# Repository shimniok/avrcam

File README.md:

# avrcam

Fork of JROBOT AVRcam by Michael Shimniok

AVRcam Hardware and Embedded Software Copyright © 2004 John Orlando
AVRcamVIEW PC Software Copyright © 2004 Brent Taylor

The AVRcam system is distributed in the hope that it will be useful. However, no warranties,
either expressed or implied, are made regarding the operation, use or results of this system. The
AVRcam should not be used in any life-critical applications.

The AVRcam is an embedded machine vision system based on an Omnivision OV6620 CMOS image sensor and ATmega microcontroller that can perform simple color
blob tracking. It is designed to be a subsystem to a more complex embedded project and uses a standard TTL serial interface. The AVRcam also comes with
standalone, cross-platform client software to interface with a computer.

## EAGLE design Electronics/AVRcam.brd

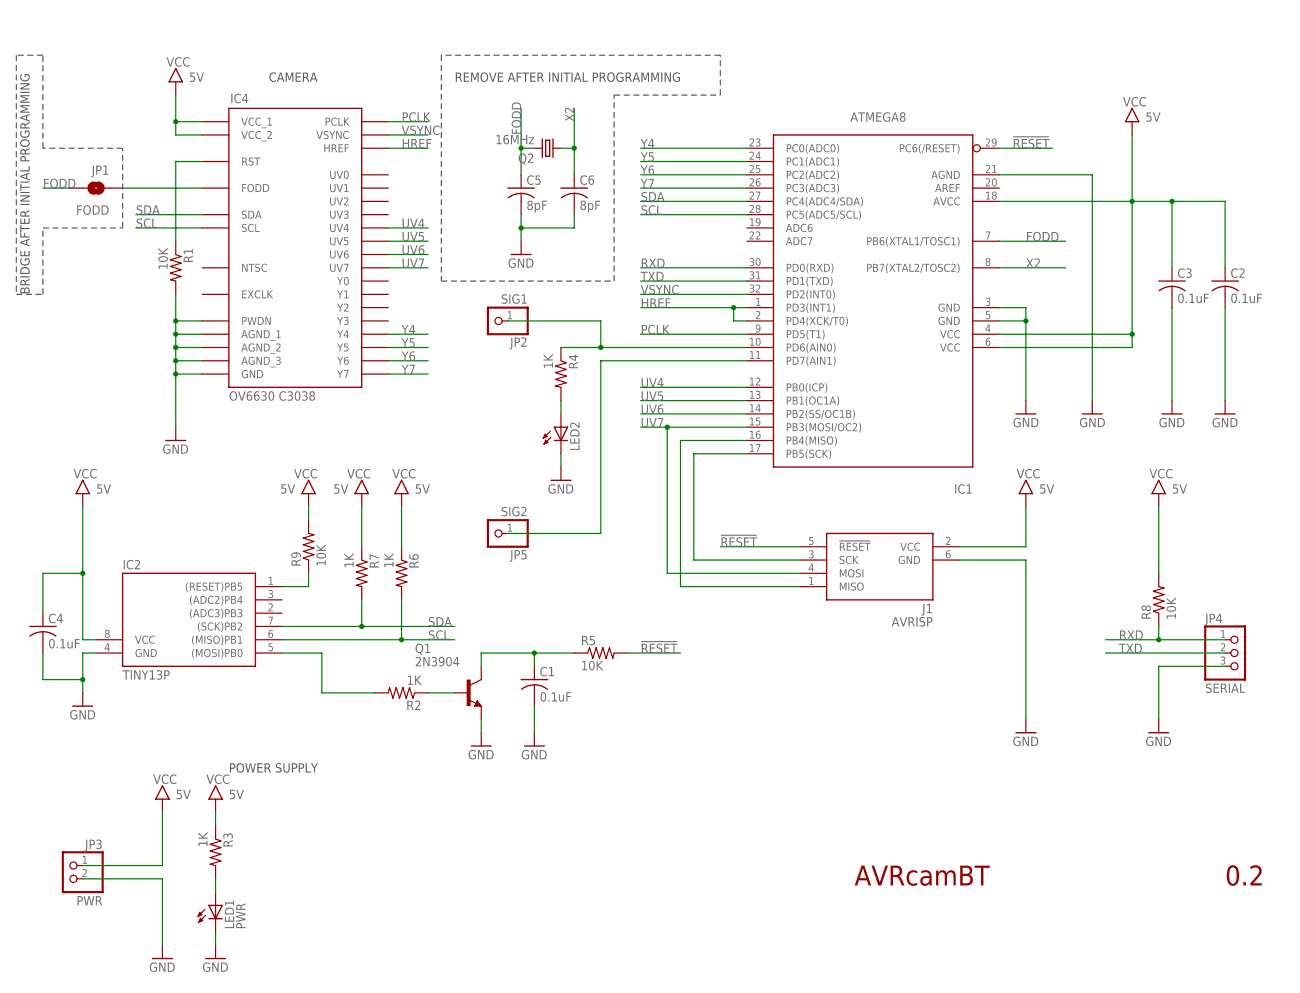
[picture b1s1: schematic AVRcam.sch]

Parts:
C1, C2, C3, C4: 0.1uF; C0603; PARTNO CC0603ZRY5V9BB104
C5, C6: 8pF; C0603; PARTNO C1608C0G1H080D
IC1: ATMEGA8; TQFP32-08; PARTNO ATMEGA8A-AU
IC2: TINY13P; DIL08; PARTNO ATTINY13V-10PU
IC4: OV6630 C3038; C3038/C3X88/C3088
J1: AVRISP; CON6P2R
JP1: FODD; SJ_2S-NO
JP2: SIG1; 1X01
JP3: PWR; 1X02-S
JP4: SERIAL; 1X03-S
JP5: SIG2; 1X01
LED1: PWR; CHIP-LED0805; PARTNO APT2012EC
LED2: LEDCHIP-LED0805; CHIP-LED0805; PARTNO APT2012SGC
Q1: 2N3904; SOT-23; PARTNO MMBT3904-7-F
Q2: 16MHz; NDK_2PAD_5X3; PARTNO NX5032GA-16.000000MHZ-LN-CD-1
R1, R5, R8, R9: 10K; R0603; PARTNO ERJ-3GEYJ103V
R2, R3, R4, R6, R7: 1K; R0603; PARTNO ERJ-3GEYJ102V

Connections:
!RESET: IC1.29 (PC6(/RESET)), J1.5 (!RESET), R5.2
FODD: C5.1, IC1.7 (PB6(XTAL1/TOSC1)), JP1.2, Q2.P$2 (2)
GND: C1.2, C2.2, C3.2, C4.2, C5.2, C6.2, IC1.3 (GND), IC1.5 (GND), IC1.21 (AGND), IC2.4 (GND), IC4.P$9 (PWDN), IC4.P$15 (AGND_1), IC4.P$17 (AGND_2), IC4.P$21 (AGND_3), IC4.P$31 (GND), J1.6 (GND), JP3.2, JP4.3, LED1.C, LED2.C, Q1.2 (E), R1.2
HREF: IC1.1 (PD3(INT1)), IC1.2 (PD4(XCK/T0)), IC4.P$14 (HREF)
MISO: IC1.16 (PB4(MISO)), J1.1 (MISO)
unnamed: C1.1, Q1.1 (C), R5.1
unnamed: IC1.11 (PD7(AIN1)), JP5.1
unnamed: LED2.A, R4.2
unnamed: IC1.10 (PD6(AIN0)), JP2.1, R4.1
unnamed: IC1.17 (PB5(SCK)), J1.3 (SCK)
unnamed: Q1.3 (B), R2.1
unnamed: LED1.A, R3.2
unnamed: IC4.P$10 (RST), R1.1
unnamed: IC4.P$12 (FODD), JP1.1
unnamed: IC2.5 ((MOSI)PB0), R2.2
unnamed: IC2.1 ((RESET)PB5), R9.1
PCLK: IC1.9 (PD5(T1)), IC4.P$18 (PCLK)
RXD: IC1.30 (PD0(RXD)), JP4.1, R8.1
SCL: IC1.28 (PC5(ADC5/SCL)), IC2.6 ((MISO)PB1), IC4.P$13 (SCL), R6.2
SDA: IC1.27 (PC4(ADC4/SDA)), IC2.7 ((SCK)PB2), IC4.P$11 (SDA), R7.2
TXD: IC1.31 (PD1(TXD)), JP4.2
UV4: IC1.12 (PB0(ICP)), IC4.P$27 (UV4)
UV5: IC1.13 (PB1(OC1A)), IC4.P$28 (UV5)
UV6: IC1.14 (PB2(SS/OC1B)), IC4.P$29 (UV6)
UV7: IC1.15 (PB3(MOSI/OC2)), IC4.P$30 (UV7), J1.4 (MOSI)
VCC: C2.1, C3.1, C4.1, IC1.4 (VCC), IC1.6 (VCC), IC1.18 (AVCC), IC2.8 (VCC), IC4.P$20 (VCC_1), IC4.P$22 (VCC_2), J1.2 (VCC), JP3.1, R3.1, R6.1, R7.1, R8.2, R9.2
VSYNC: IC1.32 (PD2(INT0)), IC4.P$16 (VSYNC)
X2: C6.1, IC1.8 (PB7(XTAL2/TOSC2)), Q2.P$1 (1)
Y4: IC1.23 (PC0(ADC0)), IC4.P$5 (Y4)
Y5: IC1.24 (PC1(ADC1)), IC4.P$6 (Y5)
Y6: IC1.25 (PC2(ADC2)), IC4.P$7 (Y6)
Y7: IC1.26 (PC3(ADC3)), IC4.P$8 (Y7)

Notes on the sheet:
AVRcamBT
0.2
POWER SUPPLY
CAMERA
REMOVE AFTER INITIAL PROGRAMMING
BRIDGE AFTER INITIAL PROGRAMMING

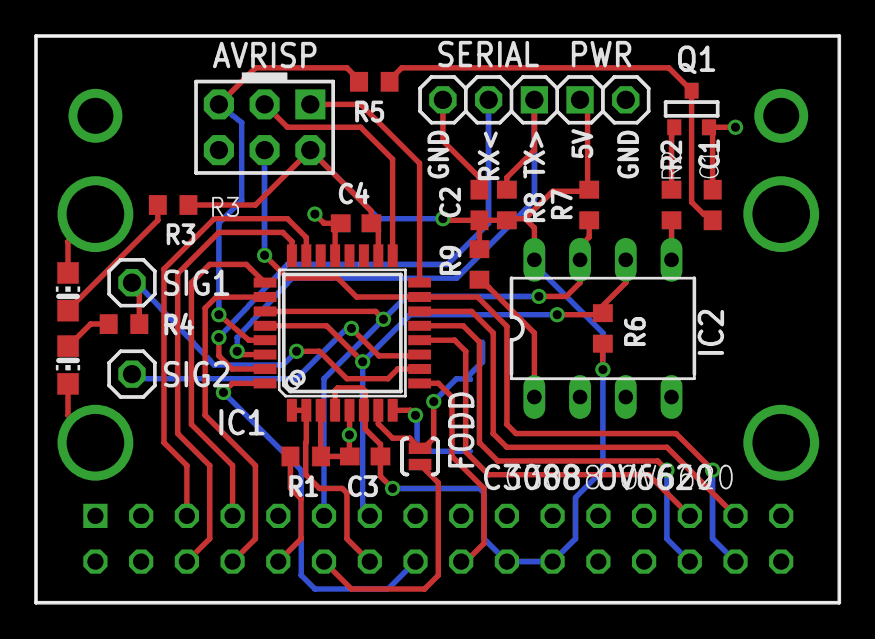
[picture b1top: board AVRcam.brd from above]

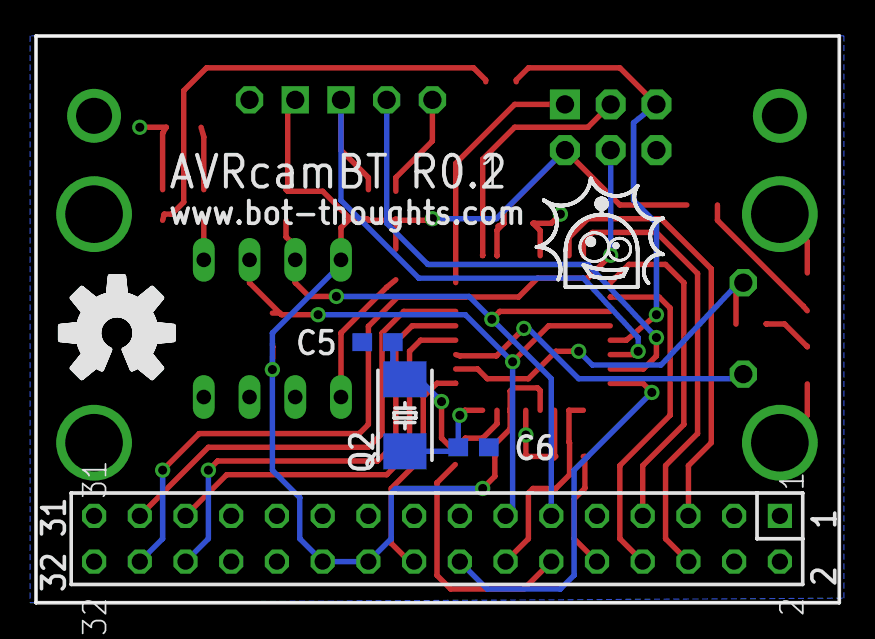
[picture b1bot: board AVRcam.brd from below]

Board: 2 copper layers, 44.6 x 31.5 mm, 28 parts (4 on the bottom side), 32 nets.

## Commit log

2012-05-16 Initial directory structure.
2012-05-16 BT AVRcam Initial Rev 0.1
2015-05-03 Migrating wiki contents from Google Code
2021-02-11 preserving crap I had laying around locally
2021-02-11 additional files added

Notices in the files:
parts and their libraries:
SparkFun: Licensing: CC v3.0 Share-Alike You are welcome to use this library for commercial purposes.
